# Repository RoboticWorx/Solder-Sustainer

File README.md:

# Solder_Sustainer
Files for my Solder Sustainer project.

Everything needed to build this project can be found on www.roboticworx.io for free! (https://roboticworx.io/blogs/projects/solder-sustainer)

**_(Remember, you can download anything you'd like for yourself but you CAN'T sell it. All my work is licensed, thanks!)_**

Thanks for reading and happy making!

Best regards,
Justin

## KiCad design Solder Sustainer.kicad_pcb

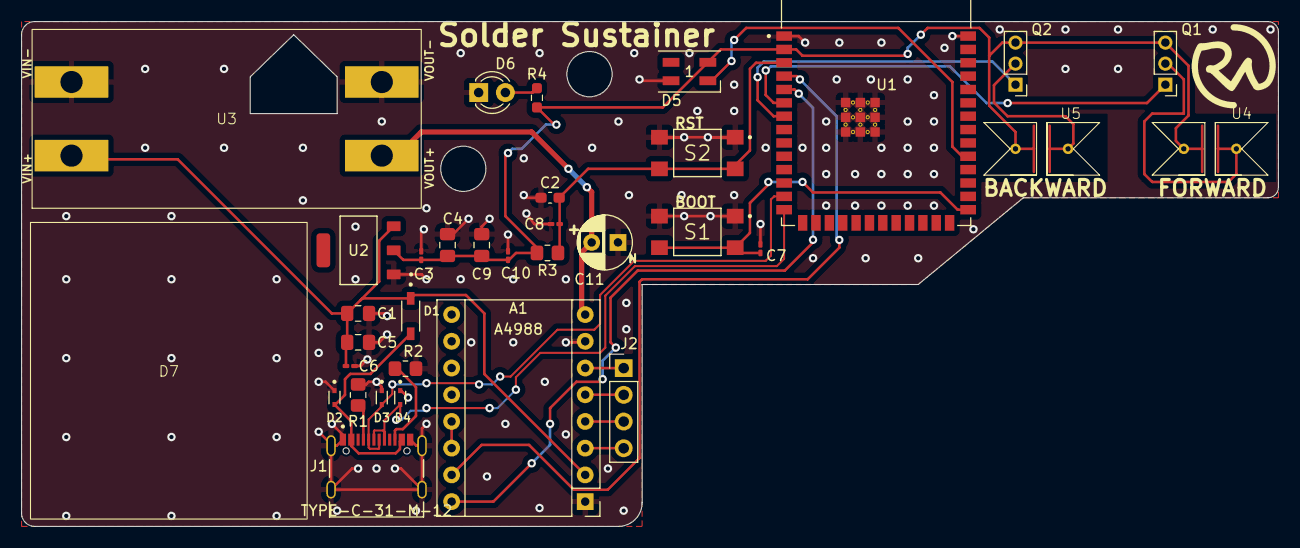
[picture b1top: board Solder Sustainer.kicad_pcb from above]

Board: 2 copper layers, 119.5 x 48.0 mm, 34 parts (0 on the bottom side), 24 nets.

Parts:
A1: Pololu_Breakout_A4988; Pololu_Breakout-16_15.2x20.3mm
C1, C4, C5, C9: 10uF/25V; C_0805_2012Metric_Pad1.18x1.45mm_HandSolder
C2: 1uF/16V; C_0603_1608Metric_Pad1.08x0.95mm_HandSolder
C3, C6, C7, C8, C10: 0u1F/50V; C_0201_0603Metric_Pad0.64x0.40mm_HandSolder
C11: 100µF; CP_Radial_D5.0mm_P2.50mm
D1: 1N5819HW-7-F; SOD3715X145N
D2, D3, D4: LESD5D5.0CT1G; TVS_LESD5D5.0CT1G
D5: SK6812MINI; LED_SK6812MINI_PLCC4_3.5x3.5mm_P1.75mm
D6: LED; LED_D3.0mm
D7: Apple Block; Outlet Rectifier
J1: TYPE-C-31-M-12; HRO_TYPE-C-31-M-12
J2: Conn_01x04_Pin; PinHeader_1x04_P2.54mm_Vertical
Q1, Q2: 2N2222; PinHeader_1x03_P2.00mm_Vertical
R1, R2: 5k1; R_0805_2012Metric_Pad1.20x1.40mm_HandSolder
R3: 10k; R_0805_2012Metric_Pad1.20x1.40mm_HandSolder
R4: 165; R_0603_1608Metric_Pad0.98x0.95mm_HandSolder
S1: TL3305BF260QG/BOOT; SW_TL3305BF260QG
S2: TL3305BF260QG/RST; SW_TL3305BF260QG
U1: ESP32-S3-WROOM-1-N16R2; XCVR_ESP32-S3-WROOM-1-N16R2
U2: AMS1117-3.3
U3: MT3608; MT3608 Breakout
U4, U5: Touch Sensor

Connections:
/CC1: J1.A5 (CC1), R1.1
/CC2: J1.B5 (CC2), R2.1
B_LOW: Q2.2 (B), U5.2 (OUT)
B_STATE: Q2.1 (E), U1.7 (IO7)
CHIP_PU: C2.2, C8.1, R3.1, S2.3, S2.4, U1.3 (EN)
D+: D4.2, J1.A6 (DP1), J1.B6 (DP2), U1.14 (IO20)
D-: D3.2, J1.A7 (DN1), J1.B7 (DN2), U1.13 (IO19)
DIR: A1.16 (DIR), U1.5 (IO5)
ESP_3V3: C3.1, C4.1, C9.1, C10.1, D5.4 (VDD), Q1.3 (C), Q2.3 (C), R3.2, R4.1, U1.2 (3V3), U2.2 (VOUT), U4.1 (VCC), U5.1 (VCC)
F_LOW: Q1.2 (B), U4.2 (OUT)
F_STATE: Q1.1 (E), U1.6 (IO6)
GND: A1.1 (GND), A1.7 (GND), C1.2, C2.1, C3.2, C4.2, C5.2, C6.2, C7.2, C8.2, C9.2, C10.2, C11.1, D2.1, D3.1, D4.1, D5.2 (VSS), D6.1 (K), J1.A1_B12 (GND), J1.B1_A12 (GND), J1.S1 (SHIELD), J1.S2 (SHIELD), J1.S3 (SHIELD), J1.S4 (SHIELD), R1.2, R2.2, S1.1, S1.2, S2.1, S2.2, U1.1 (GND), U1.40 (GND), U1.41_1 (GND), U1.41_2 (GND), U1.41_3 (GND), U1.41_4 (GND), U1.41_5 (GND), U1.41_6 (GND), U1.41_7 (GND), U1.41_8 (GND), U1.41_9 (GND), U1.41_10, U1.41_11, U1.41_12, U1.41_13, U1.41_14, U1.41_15, U1.41_16, U1.41_17, U1.41_18, U1.41_19, U1.41_20, U1.41_21, U2.1 (GND/ADJ), U3.2 (GND), U3.3 (FB)
GPIO0: C7.1, S1.3, S1.4, U1.27 (IO0)
unnamed: A1.4 (1A), J2.3
unnamed: A1.3 (1B), J2.4
unnamed: A1.5 (2A), J2.2
unnamed: A1.6 (2B), J2.1
unnamed: A1.13 (~RESET), A1.14 (~SLEEP)
unnamed: D1.A, D2.2, J1.A4_B9 (VBUS), J1.B4_A9 (VBUS)
unnamed: D6.2 (A), R4.2
SK6812: D5.3 (DIN), U1.31 (IO38)
STEP: A1.15 (STEP), U1.4 (IO4)
VCC_5V: A1.2 (VDD), C1.1, C5.1, C6.1, D1.C, U2.3 (VIN), U3.5 (IN)
VMOT: A1.8 (VMOT), C11.2, U3.1 (SW)

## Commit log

2023-07-20 Add files via upload
    KiCad Schematic file.
2023-07-20 SMD BOM
    SMD components description, values, footprints, and more.
2023-07-26 Fabrication File for the PCB
2023-07-27 Solder Sustainer Gerber File For Fabrication
2023-07-27 Gerber File for Fabrication
2023-07-27 Wiring Schematic (Image)
2023-07-27 KiCad Files for Schematic and PCB
2023-07-27 Create The Program
2023-07-27 The Program
    Program for my solder sustainer project
2023-07-27 The Programming
2023-07-28 Component Part List
2023-07-28 SMD Symbols For PCB Assembly
